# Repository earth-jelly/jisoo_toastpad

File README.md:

# ToastPad
*"Because I couldn't cad a croissant."*

## Overview
My personal macropad designed for all sound stuff that I need on a daily basis, inspired by Heidi, Orpheus, and toast.

---
### BOM
| QUANTITY | ITEM |
|---|---|
| 1 | Seeed XIAO RP2040 |
| 5 | MX-Style switches |
| 1 | EC11 Rotary encoders |
| 1 | 0.91 inch OLED displays |
| 5 | Blank DSA keycaps |
| 5 | MX-Style switches |
| 5 | MINI-E LEDs |
| 3 | M3x16mm screws |
| 3 | M3x5mx4mm heatset inserts |
| 1 | 3D printed case (2 parts) |

---
### Schemetics

---
### PCB

The silkscreen art on the back was created during 2 days of Blueprint Prototype lock-in call, combining favorite animals/creatures of the Hackclubbers in the call.

---
### Firmware
Toastpad uses KMK firmware to operate. 
It currently supports media pause & play, fast forward & backward, skipping to next/prev. track, volume control, and displaying music streaming service inpired icons!

---
### Final disclaimer
The Toastpad is as flimsy as a wet toast and operates on hopes and dreams.

Do __*NOT*__:
  - expect it to work on the first try
  - blame me for any malfunctions (because I already warned you)
  - try to eat it

Thank you :>

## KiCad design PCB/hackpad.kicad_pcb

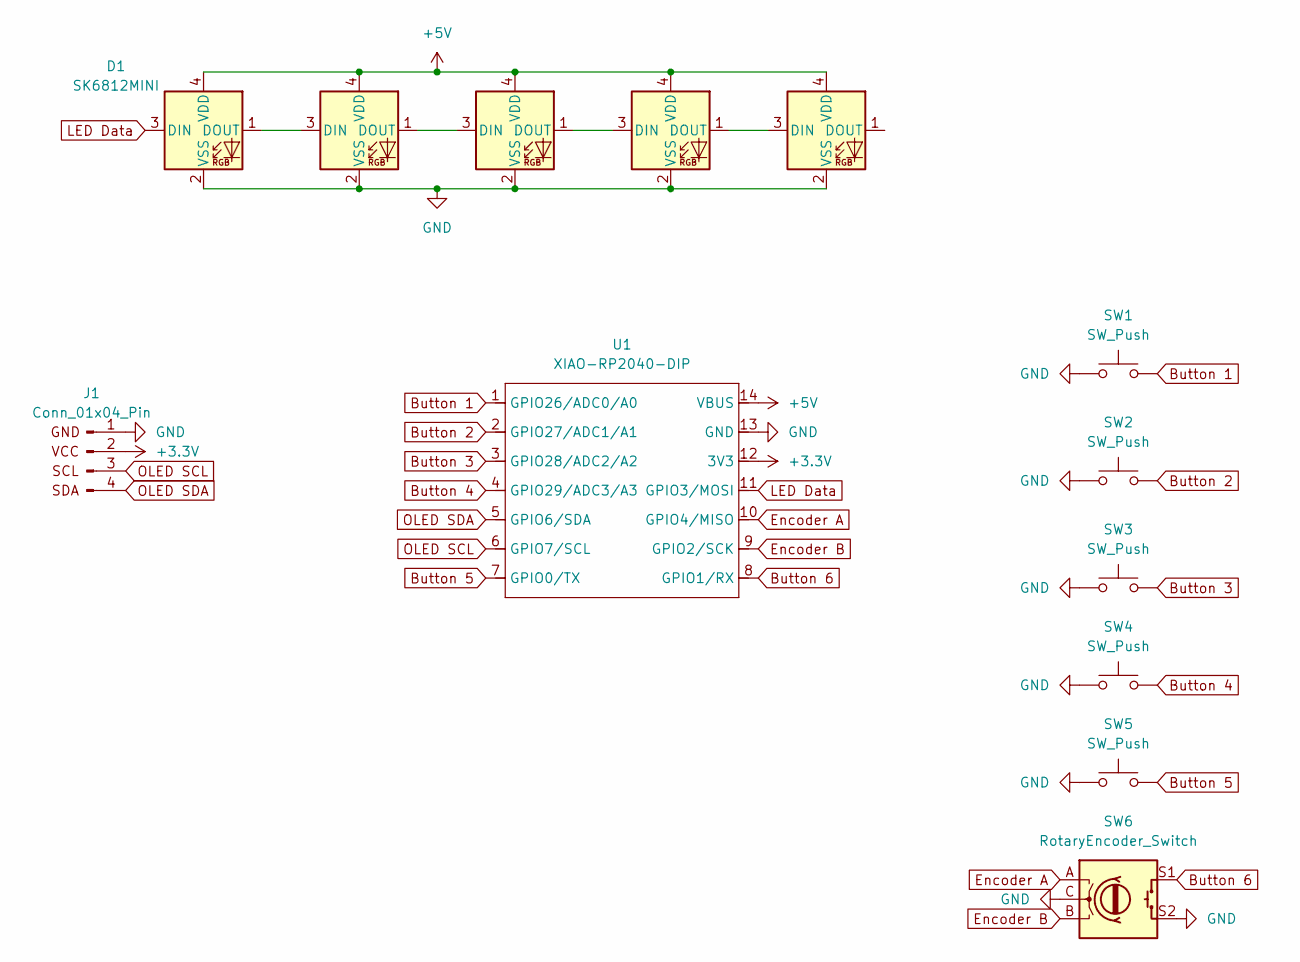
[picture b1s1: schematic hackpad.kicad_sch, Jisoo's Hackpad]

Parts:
D1, D2, D3, D4, D5: SK6812MINI; MX_SK6812MINI-E_REV(1)
J1: Conn_01x04_Pin; SSD1306-0.91-OLED-4pin-128x32
SW1, SW2, SW3, SW4, SW5: SW_Push; cherry_mx_1.00u_pcb_custom
SW6: RotaryEncoder_Switch; Rotary_EncoderRotaryEncoder_Alps_EC11E-Switch_Vertical_H20m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
U1: XIAO-RP2040-DIP

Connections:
+3.3V: J1.2, U1.12 (3V3)
+5V: D1.4 (VDD), D2.4 (VDD), D3.4 (VDD), D4.4 (VDD), D5.4 (VDD), U1.14 (VBUS)
Button 1: SW1.2, U1.1 (GPIO26/ADC0/A0)
Button 2: SW2.2, U1.2 (GPIO27/ADC1/A1)
Button 3: SW3.2, U1.3 (GPIO28/ADC2/A2)
Button 4: SW4.2, U1.4 (GPIO29/ADC3/A3)
Button 5: SW5.2, U1.7 (GPIO0/TX)
Button 6: SW6.S1, U1.8 (GPIO1/RX)
Encoder A: SW6.A, U1.10 (GPIO4/MISO)
Encoder B: SW6.B, U1.9 (GPIO2/SCK)
GND: D1.2 (VSS), D2.2 (VSS), D3.2 (VSS), D4.2 (VSS), D5.2 (VSS), J1.1, SW1.1, SW2.1, SW3.1, SW4.1, SW5.1, SW6.C, SW6.S2, U1.13 (GND)
LED Data: D1.3 (DIN), U1.11 (GPIO3/MOSI)
unnamed: D1.1 (DOUT), D2.3 (DIN)
unnamed: D2.1 (DOUT), D3.3 (DIN)
unnamed: D3.1 (DOUT), D4.3 (DIN)
unnamed: D4.1 (DOUT), D5.3 (DIN)
OLED SCL: J1.3, U1.6 (GPIO7/SCL)
OLED SDA: J1.4, U1.5 (GPIO6/SDA)

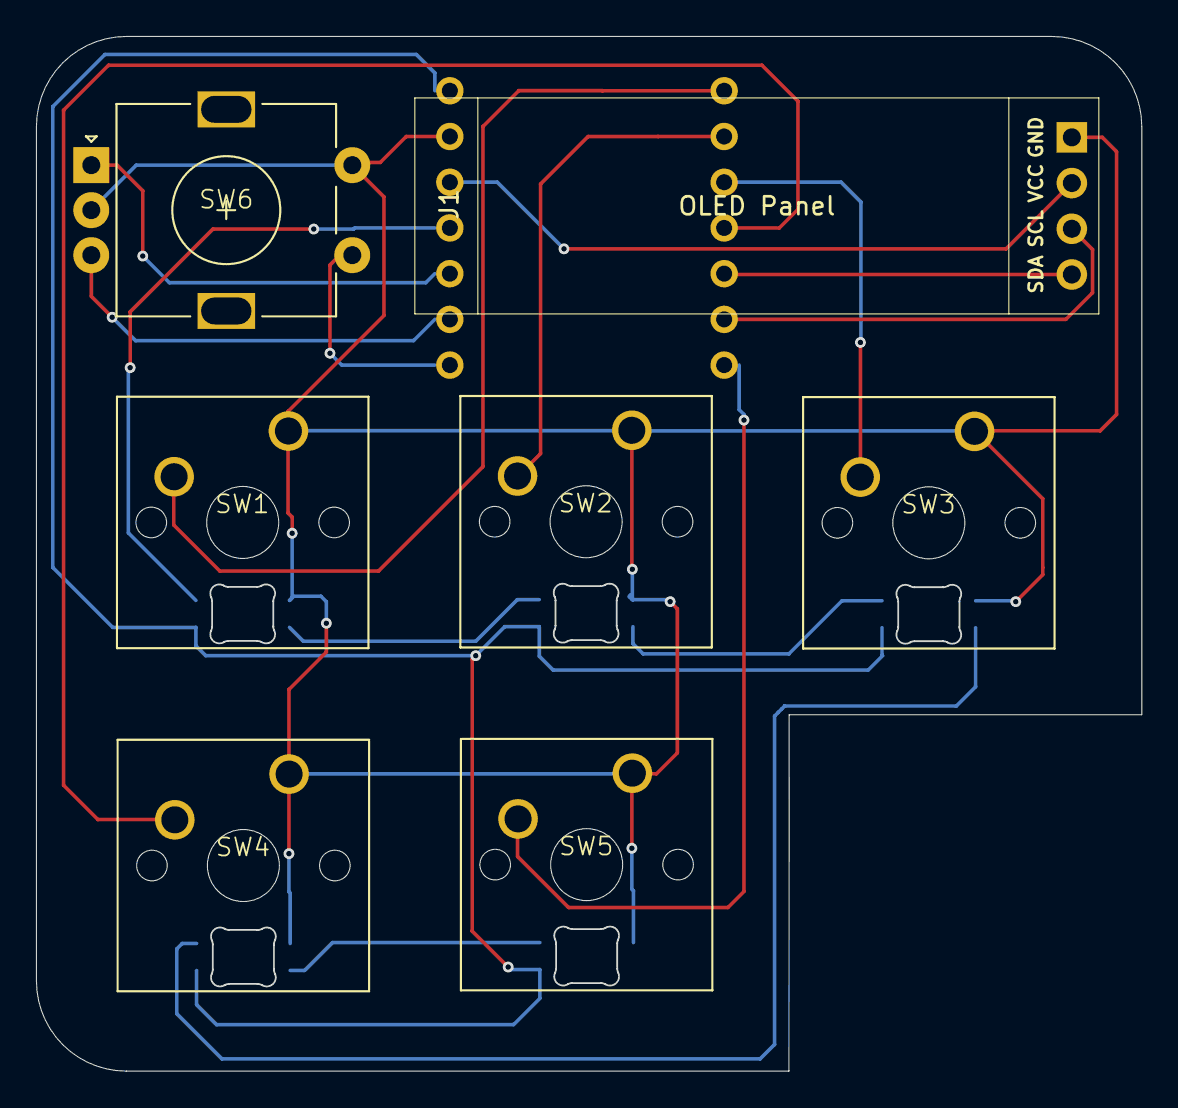
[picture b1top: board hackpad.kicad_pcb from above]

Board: 2 copper layers, 61.4 x 57.4 mm, 13 parts (1 on the bottom side), 18 nets.

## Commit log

2025-11-22 hackpad??
    im so lost
2025-11-22 Update README.md
    hehe
2025-11-23 Update README.md
    Silkscreen + finished routing
2025-11-29 updates from the last 4 days
    mostly 3d models for cad stuff and kicad mod..?
2025-12-06 A lot of things (the basic structure)
2025-12-16 Update main.py
    Fixed OLED display
2026-02-03 Added CAD file and relocated some
2026-02-03 Partial update to README.md
2026-02-03 hopefully a final update of README.md
2026-02-03 Please final README.md update
    OKAY PLEASE LET THIS BE THE LAST CHANGE
2026-02-03 updated the pcb image
2026-02-03 grammar check ;-;
2026-02-03 formatting change for disclaimer
2026-02-24 code update
